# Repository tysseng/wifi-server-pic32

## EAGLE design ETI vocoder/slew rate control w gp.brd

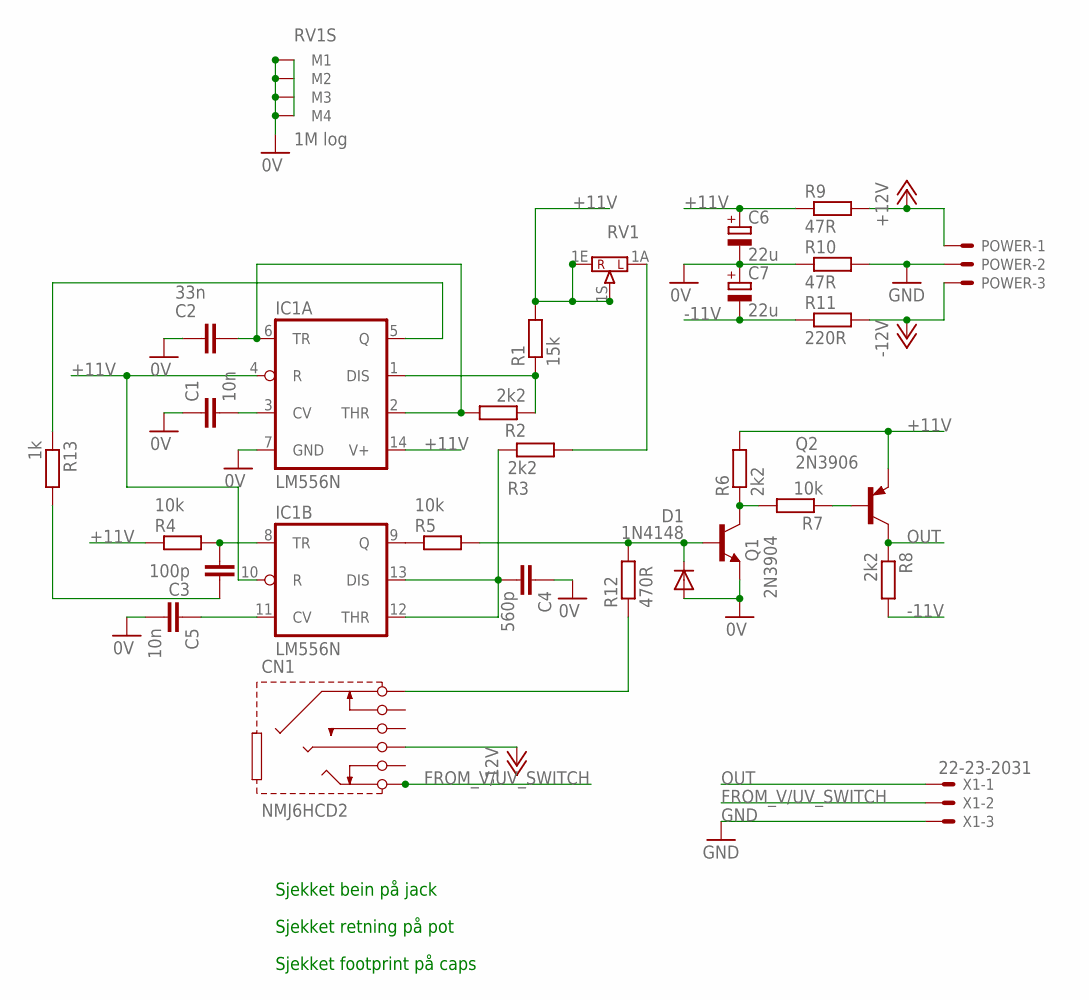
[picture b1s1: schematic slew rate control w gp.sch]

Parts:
C1, C5: 10n; C025-025X050
C2: 33n; C075-032X103
C3: 100p; C025-025X050
C4: 560p; C025-025X050
C6, C7: 22u; E2,5-5
CN1: NMJ6HCD2
D1: 1N4148; DO35-5J
IC1: LM556N; DIL14
POWER: KK-156-3
Q1: 2N3904; TO92
Q2: 2N3906; TO92
R1: 15k; 0207/7
R2, R3, R6, R8: 2k2; 0207/7
R4, R5, R7: 10k; 0207/7
R9, R10: 47R; 0207/7
R11: 220R; 0207/7
R12: 470R; 0207/7
R13: 1k; 0207/7
RV1: 1M log; POT16_W_BRACKET
X1: 22-23-2031

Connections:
0V: C1.1, C2.2, C4.1, C5.2, C6.-, C7.+, D1.A, IC1.7 (GND), Q1.3 (E), R10.1, RV1.M1, RV1.M2, RV1.M3, RV1.M4
+11V: C6.+, IC1.4 (R), IC1.10 (R), IC1.14 (V+), Q2.3 (E), R1.2, R4.1, R6.2, R9.1, RV1.1E, RV1.1S
+12V: POWER.1, R9.2
-11V: C7.-, R8.2, R11.1
-12V: CN1.R (RING), POWER.3, R11.2
FROM_V/UV_SWITCH: CN1.T (TIP), X1.2
GND: POWER.2, R10.2, X1.3
unnamed: C3.2, IC1.8 (TR), R4.2
unnamed: C2.1, IC1.2 (THR), IC1.6 (TR), R2.2
unnamed: C5.1, IC1.11 (CV)
unnamed: IC1.9 (Q), R5.1
unnamed: C4.2, IC1.12 (THR), IC1.13 (DIS), R3.1
unnamed: C3.1, R13.2
unnamed: IC1.5 (Q), R13.1
unnamed: R3.2, RV1.1A
unnamed: IC1.1 (DIS), R1.1, R2.1
unnamed: C1.2, IC1.3 (CV)
unnamed: D1.C, Q1.2 (B), R5.2, R12.2
unnamed: CN1.S (SLEEVE), R12.1
unnamed: Q1.1 (C), R6.1, R7.2
unnamed: Q2.2 (B), R7.1
OUT: Q2.1 (C), R8.1, X1.1

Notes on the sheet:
Sjekket retning på pot
Sjekket bein på jack
Sjekket footprint på caps

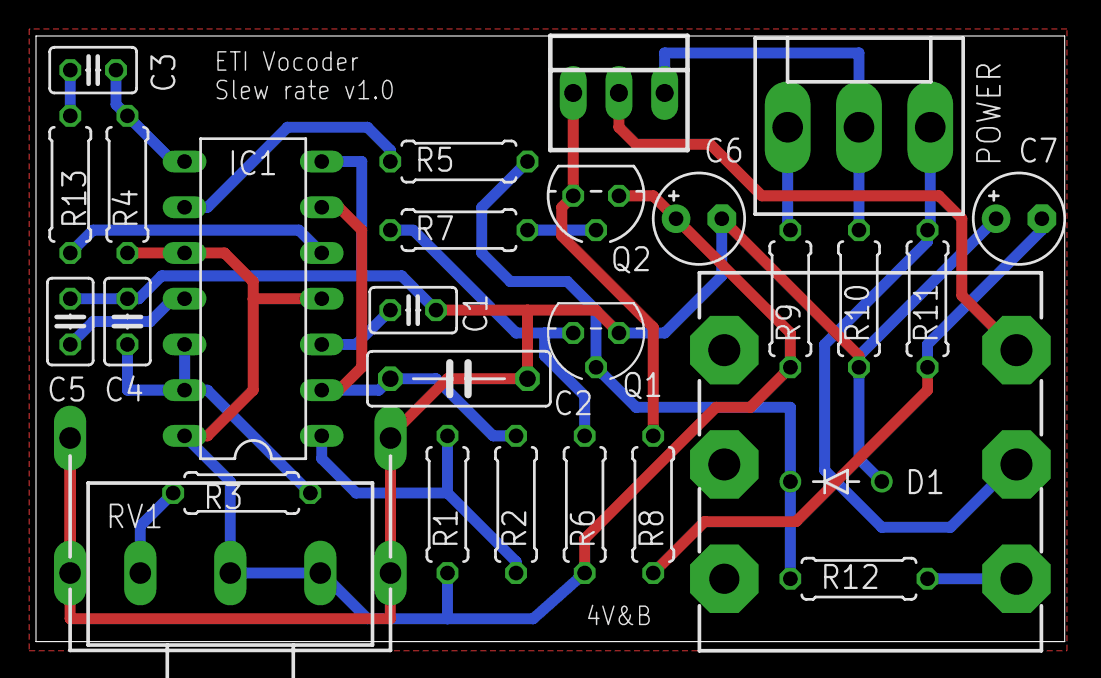
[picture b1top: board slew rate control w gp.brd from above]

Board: 2 copper layers, 57.1 x 33.6 mm, 28 parts (0 on the bottom side), 22 nets.

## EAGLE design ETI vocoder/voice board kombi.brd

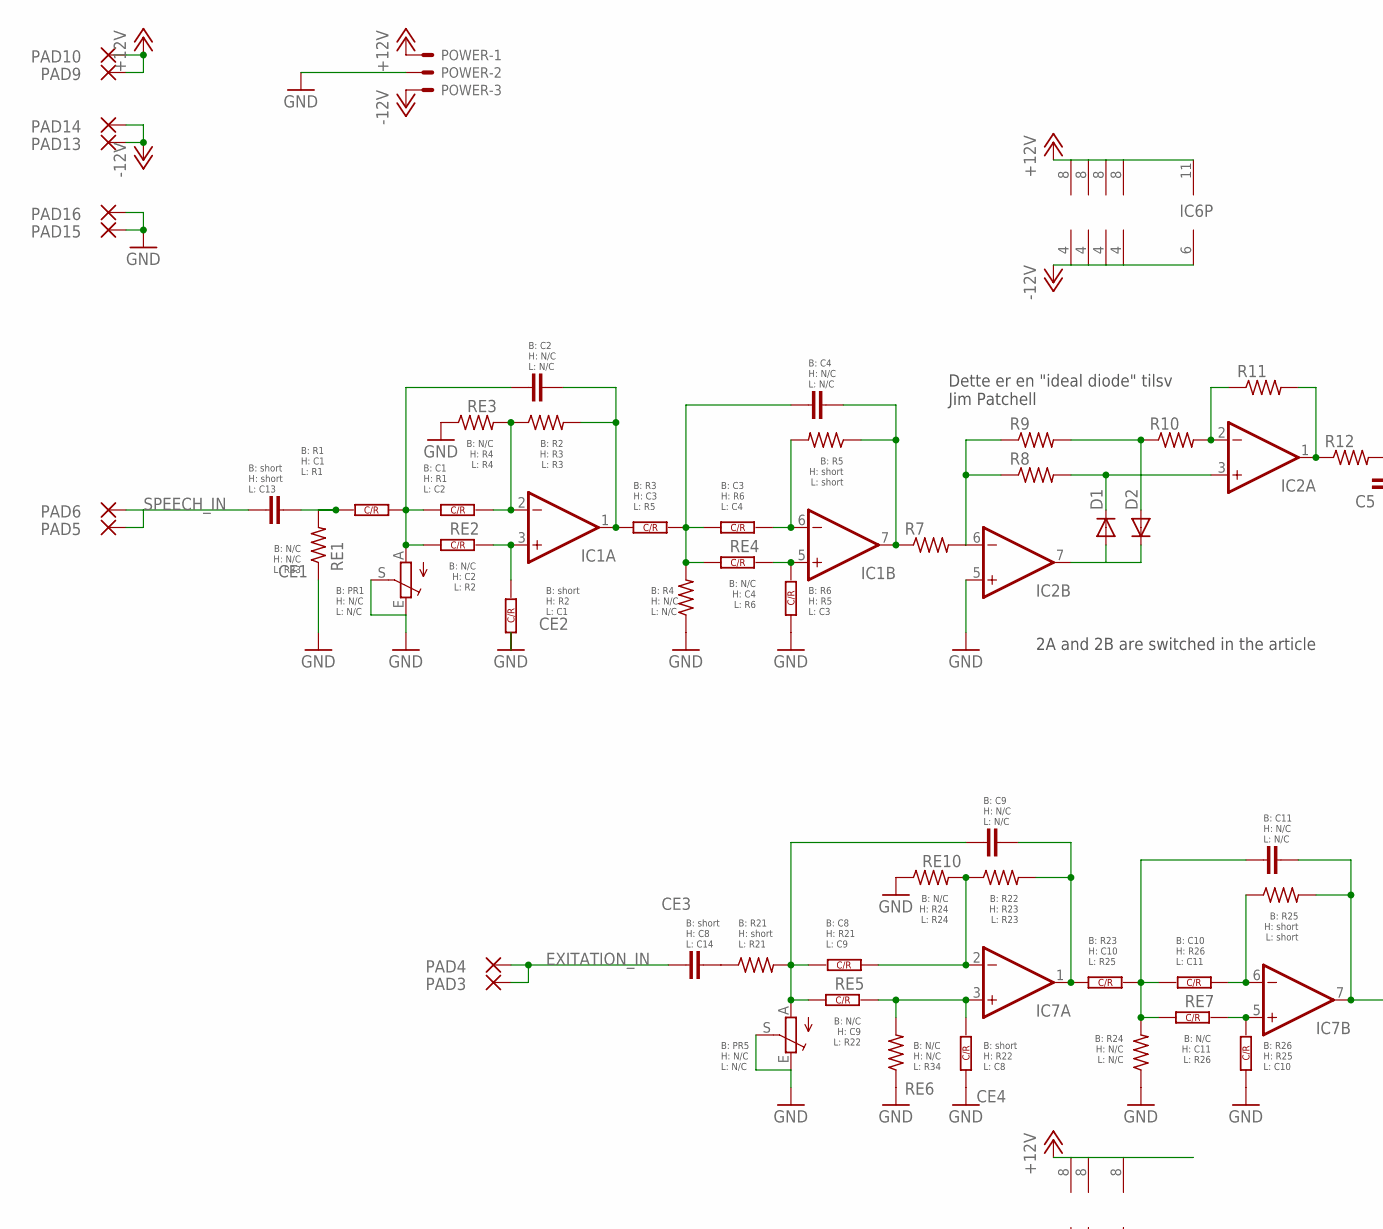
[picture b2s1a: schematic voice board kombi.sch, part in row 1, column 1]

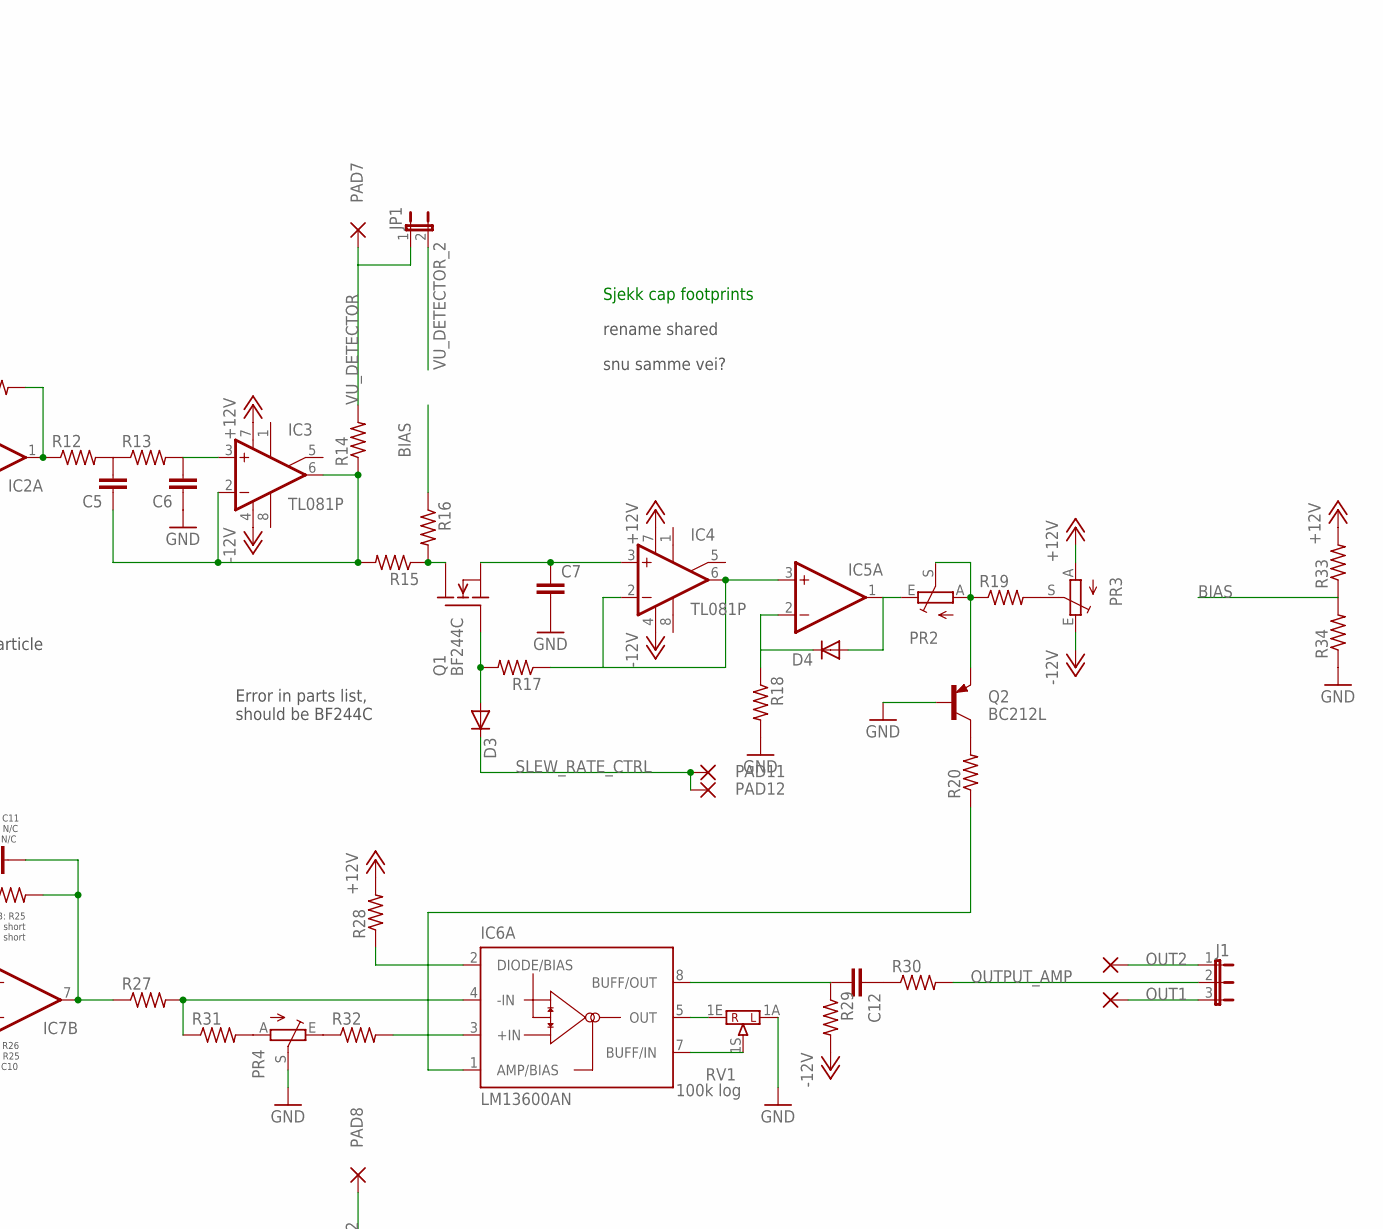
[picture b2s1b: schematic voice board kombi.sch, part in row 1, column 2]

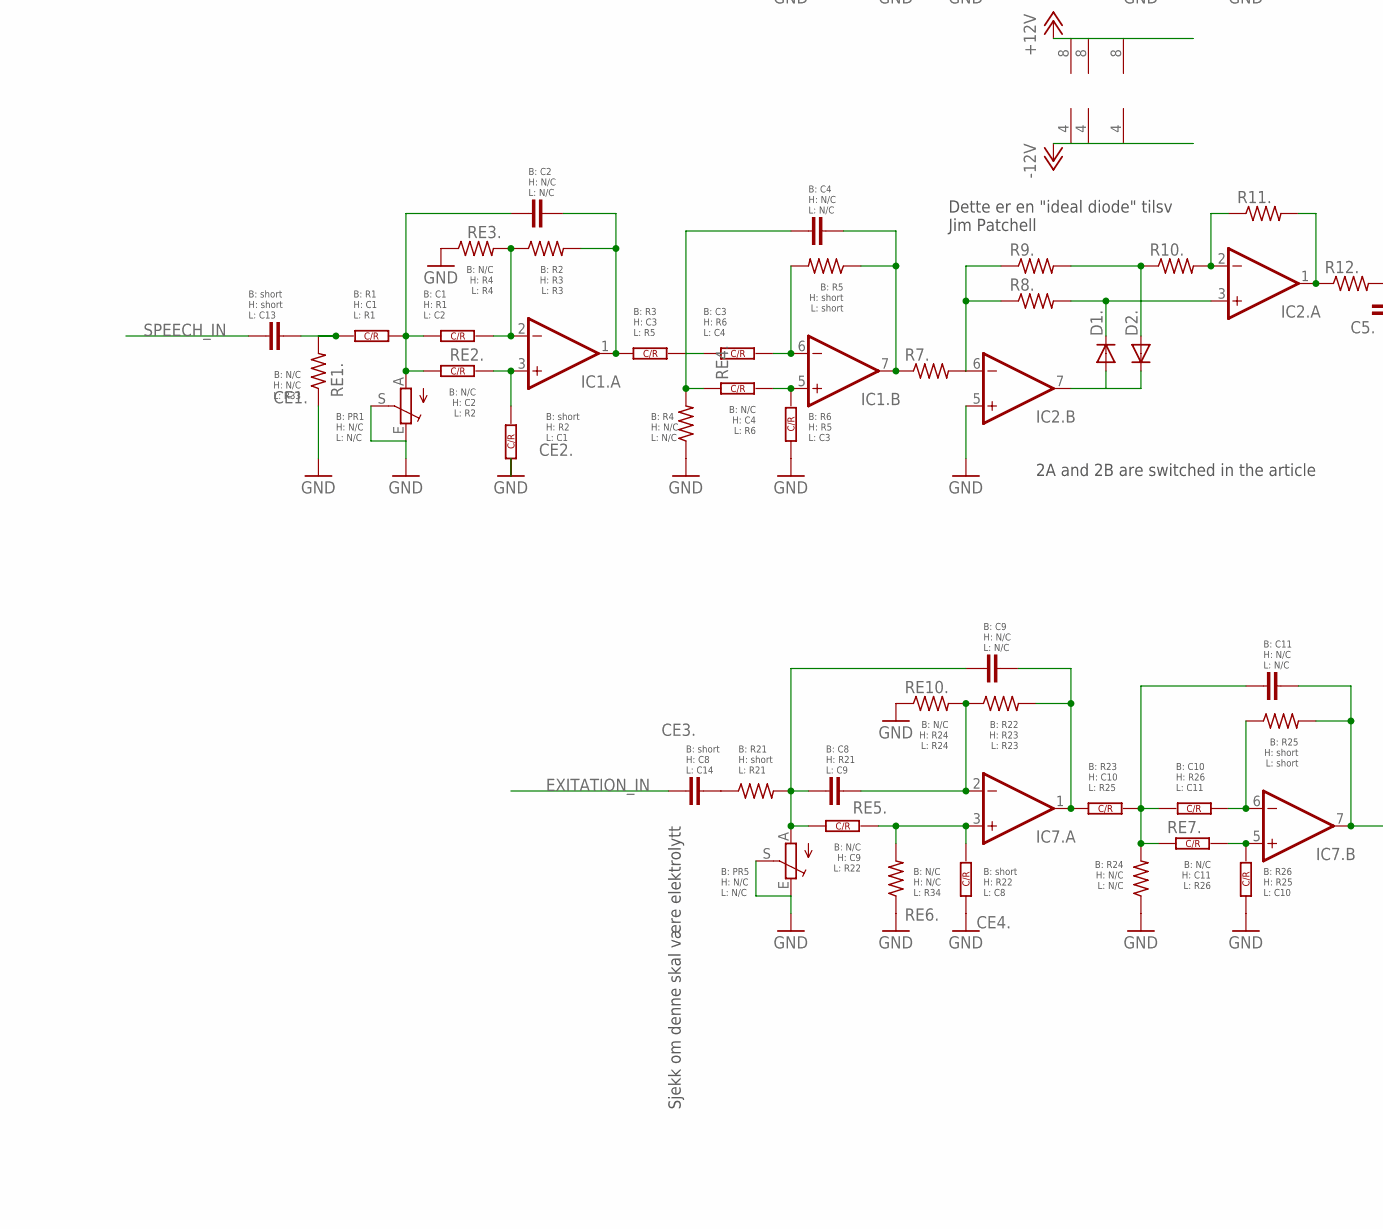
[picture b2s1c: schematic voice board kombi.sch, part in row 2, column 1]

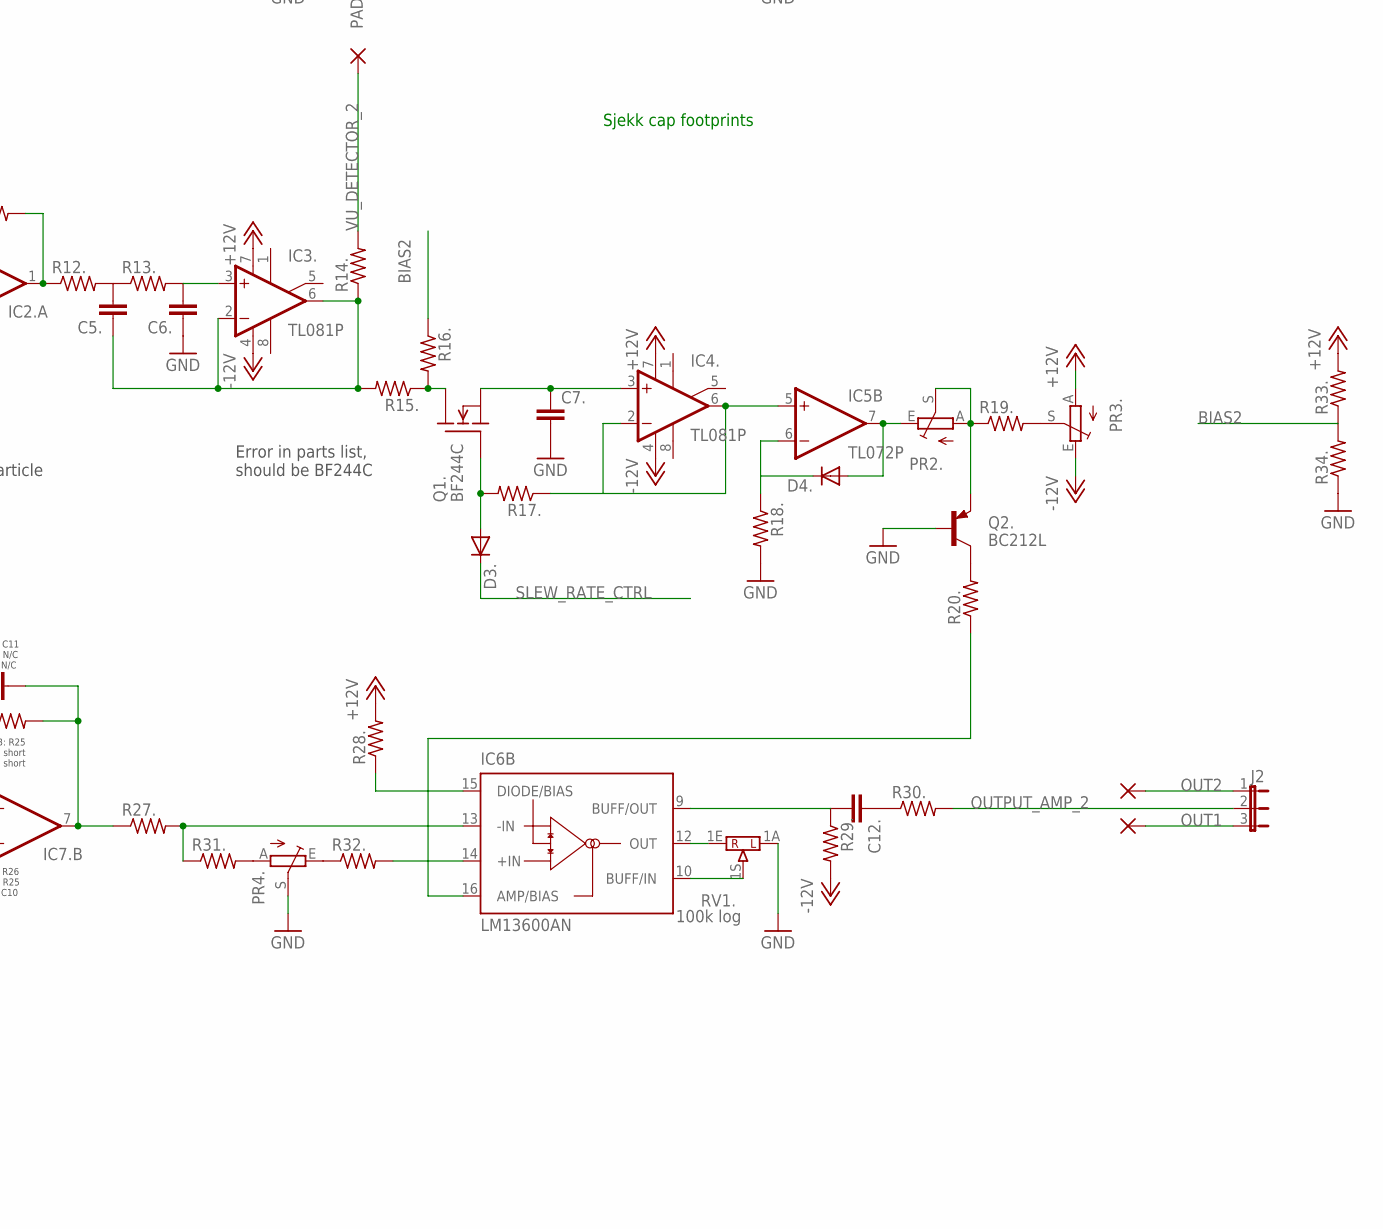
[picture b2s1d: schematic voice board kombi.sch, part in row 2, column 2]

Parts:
C1, C1., C3, C3., C8, C10, C10.: C-OR-R050_075-025X100; P050_075-025X100J
C2, C2., C4, C4., C5, C5., C6, C6., C7, C7., C8., C9, C9., C11, C11., C12, C12.: C-EU050_075-025X100; C050_075-025X100J
CE1, CE1., CE3, CE3.: C-EU050_075-025X100; C050_075-025X100J
CE2, CE2., CE4, CE4.: C-OR-R050_075-025X100; P050_075-025X100J
D1, D1., D2, D2., D3, D3., D4, D4.: DIODE-D-5; D-5
IC1, IC1., IC2, IC2., IC5, IC7, IC7.: TL072P; DIL08
IC3, IC3., IC4, IC4.: TL081P; DIL08
IC6: LM13600AN; DIL16
J1, J2: JP2E; JP2
JP1: JP1E; JP1
PAD1, PAD2, PAD3, PAD4, PAD5, PAD6, PAD7, PAD8, PAD9, PAD10, PAD11, PAD12, PAD13, PAD14, PAD15, PAD16, PAD17, PAD18: WIREPAD2,54/1,1; 2,54/1,1
POWER: KK-156-3
PR1, PR1., PR2, PR2., PR3, PR3., PR4, PR4., PR5, PR5.: TRIM_EU-CA9V; CA9V
Q1, Q1.: BF244C; TO-92
Q2, Q2.: BC212L; TO92-ECB
R1, R1., R3, R3., R6, R6., R23, R23., R26, R26.: C-OR-R050_075-025X100; P050_075-025X100J
R2, R2., R4, R4., R5, R5., R7, R7., R8, R8., R9, R9., R10, R10., R11, R11., R12, R12., R13, R13., R14, R14., R15, R15., R16, R16., R17, R17., R18, R18., R19, R19., R20, R20., R21, R21., R22, R22., R24, R24., R25, R25., R27, R27., R28, R28., R29, R29., R30, R30., R31, R31., R32, R32., R33, R33., R34, R34.: R-US_0207/7; 0207/7
RE1, RE1., RE3, RE3., RE6, RE6., RE10, RE10.: R-US_0207/7; 0207/7
RE2, RE2., RE4, RE4., RE5, RE5., RE7, RE7.: C-OR-R050_075-025X100; P050_075-025X100J
RV1, RV1.: 100k log; POT16_W_BRACKET

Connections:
+12V: IC1.8 (V+), IC1..8 (V+), IC2.8 (V+), IC2..8 (V+), IC3.7 (V+), IC3..7 (V+), IC4.7 (V+), IC4..7 (V+), IC5.8 (V+), IC6.11 (V+), IC7.8 (V+), IC7..8 (V+), PAD9.1, PAD10.1, POWER.1, PR3.A, PR3..A, R28.2, R28..2, R33.2, R33..2
-12V: IC1.4 (V-), IC1..4 (V-), IC2.4 (V-), IC2..4 (V-), IC3.4 (V-), IC3..4 (V-), IC4.4 (V-), IC4..4 (V-), IC5.4 (V-), IC6.6 (V-), IC7.4 (V-), IC7..4 (V-), PAD13.1, PAD14.1, POWER.3, PR3.E, PR3..E, R29.2, R29..2
BIAS: R16.1, R33.1, R34.2
BIAS2: R16..1, R33..1, R34..2
EXITATION_IN: CE3.1, CE3..1, PAD3.1, PAD4.1
GND: C6.1, C6..1, C7.2, C7.3 (2), C7..2, C7..3 (2), CE2.1, CE2..1, CE4.1, CE4..1, IC2.5 (+IN), IC2..5 (+IN), PAD15.1, PAD16.1, POWER.2, PR1.E, PR1.S, PR1..E, PR1..S, PR4.S, PR4..S, PR5.E, PR5.S, PR5..E, PR5..S, Q2.B, Q2..B, R4.1, R4..1, R6.1, R6..1, R18.2, R18..2, R24.1, R24..1, R26.1, R26..1, R34.1, R34..1, RE1.1, RE1..1, RE3.1, RE3..1, RE6.1, RE6..1, RE10.1, RE10..1, RV1.1A, RV1..1A
unnamed: C1.2, C1.3 (2), IC1.2 (-IN), R2.1, RE3.2
unnamed: C1.1, C2.1, PR1.A, R1.1, RE2.1
unnamed: C2.2, C2.3 (2), IC1.1 (OUT), R2.2, R3.1
unnamed: IC2.6 (-IN), R7.2, R8.1, R9.1
unnamed: C3.1, C4.1, R3.2, R3.3 (2), R4.2, RE4.1
unnamed: C3.2, C3.3 (2), IC1.6 (-IN), R5.2
unnamed: IC1.5 (+IN), R6.2, R6.3 (2), RE4.2, RE4.3 (2)
unnamed: C4.2, C4.3 (2), IC1.7 (OUT), R5.1, R7.1
unnamed: D1.C, IC2.3 (+IN), R8.2
unnamed: D1.A, D2.C, IC2.7 (OUT)
unnamed: D2.A, R9.2, R10.1
unnamed: IC2.2 (-IN), R10.2, R11.1
unnamed: IC2.1 (OUT), R11.2, R12.1
unnamed: C5.2, C5.3 (2), R12.2, R13.1
unnamed: C5.1, IC3.2 (-IN), IC3.6 (OUT), R14.1, R15.2
unnamed: C6.2, C6.3 (2), IC3.3 (+IN), R13.2
unnamed: Q1.3 (D), R15.1, R16.2
unnamed: C7.1, IC4.3 (+IN), Q1.1 (S)
unnamed: D3.A, Q1.2 (G), R17.2
unnamed: IC4.2 (-IN), IC4.6 (OUT), IC5.3 (+IN), R17.1
unnamed: D4.C, IC5.2 (-IN), R18.1
unnamed: D4.A, IC5.1 (OUT), PR2.E
unnamed: PR2.A, PR2.S, Q2.E, R19.1
unnamed: PR3.S, R19.2
unnamed: Q2.C, R20.2
unnamed: PR4.A, R31.2
unnamed: C8.2, C8.3 (2), C9.2, C9.3 (2), PR5.A, R21.2, RE5.1
unnamed: C10.2, C10.3 (2), C11.2, C11.3 (2), R23.2, R23.3 (2), R24.2, RE7.1
unnamed: C8.1, IC7.2 (-IN), R22.1, RE10.2
unnamed: C9.1, IC7.1 (OUT), R22.2, R23.1
unnamed: C10.1, IC7.6 (-IN), R25.1
unnamed: IC7.5 (+IN), R26.2, R26.3 (2), RE7.2, RE7.3 (2)
unnamed: C12.2, C12.3 (2), IC6.8 (BUFF/OUT), R29.1
unnamed: C12.1, R30.1
unnamed: C11.1, IC7.7 (OUT), R25.2, R27.1
unnamed: PR4.E, R32.1
unnamed: IC6.3 (+IN), R32.2
unnamed: IC6.2 (DIODE/BIAS), R28.1
unnamed: IC6.4 (-IN), R27.2, R31.1
unnamed: IC6.1 (AMP/BIAS), R20.1
unnamed: IC6.5 (OUT), RV1.1E
unnamed: IC6.7 (BUFF/IN), RV1.1S
unnamed: CE1.1, R1.2, R1.3 (2), RE1.2
unnamed: CE2.2, CE2.3 (2), IC1.3 (+IN), RE2.2, RE2.3 (2)
unnamed: CE3.2, CE3.3 (2), R21.1
unnamed: CE4.2, CE4.3 (2), IC7.3 (+IN), RE5.2, RE5.3 (2), RE6.2
unnamed: C1..2, C1..3 (2), IC1..2 (-IN), R2..1, RE3..2
unnamed: C1..1, C2..1, PR1..A, R1..1, RE2..1
unnamed: C2..2, C2..3 (2), IC1..1 (OUT), R2..2, R3..1
unnamed: C3..1, C4..1, R3..2, R3..3 (2), R4..2, RE4..1
unnamed: C3..2, C3..3 (2), IC1..6 (-IN), R5..2
unnamed: IC1..5 (+IN), R6..2, R6..3 (2), RE4..2, RE4..3 (2)
unnamed: C4..2, C4..3 (2), IC1..7 (OUT), R5..1, R7..1
unnamed: IC2..6 (-IN), R7..2, R8..1, R9..1
unnamed: D1..C, IC2..3 (+IN), R8..2
unnamed: D1..A, D2..C, IC2..7 (OUT)
unnamed: D2..A, R9..2, R10..1
unnamed: IC2..2 (-IN), R10..2, R11..1
unnamed: IC2..1 (OUT), R11..2, R12..1
unnamed: C5..2, C5..3 (2), R12..2, R13..1
unnamed: C5..1, IC3..2 (-IN), IC3..6 (OUT), R14..1, R15..2
unnamed: C6..2, C6..3 (2), IC3..3 (+IN), R13..2
unnamed: Q1..3 (D), R15..1, R16..2
unnamed: C7..1, IC4..3 (+IN), Q1..1 (S)
unnamed: D3..A, Q1..2 (G), R17..2
unnamed: IC4..2 (-IN), IC4..6 (OUT), IC5.5 (+IN), R17..1
unnamed: D4..C, IC5.6 (-IN), R18..1
unnamed: D4..A, IC5.7 (OUT), PR2..E
unnamed: PR2..A, PR2..S, Q2..E, R19..1
unnamed: PR3..S, R19..2
unnamed: Q2..C, R20..2
unnamed: PR4..A, R31..2
unnamed: C8..2, C8..3 (2), C9..2, C9..3 (2), PR5..A, R21..2, RE5..1
unnamed: C10..2, C10..3 (2), C11..2, C11..3 (2), R23..2, R23..3 (2), R24..2, RE7..1
unnamed: C8..1, IC7..2 (-IN), R22..1, RE10..2
unnamed: C9..1, IC7..1 (OUT), R22..2, R23..1
unnamed: C11..1, IC7..7 (OUT), R25..2, R27..1
unnamed: PR4..E, R32..1
unnamed: IC6.14 (+IN), R32..2
unnamed: IC6.15 (DIODE/BIAS), R28..1
unnamed: IC6.13 (-IN), R27..2, R31..1
unnamed: IC6.16 (AMP/BIAS), R20..1
unnamed: IC6.10 (BUFF/IN), RV1..1S
unnamed: C12..2, C12..3 (2), IC6.9 (BUFF/OUT), R29..1
unnamed: C12..1, R30..1
unnamed: C10..1, IC7..6 (-IN), R25..1
unnamed: IC7..5 (+IN), R26..2, R26..3 (2), RE7..2, RE7..3 (2)
unnamed: CE1..1, R1..2, R1..3 (2), RE1..2
unnamed: CE2..2, CE2..3 (2), IC1..3 (+IN), RE2..2, RE2..3 (2)
unnamed: CE3..2, CE3..3 (2), R21..1
unnamed: CE4..2, CE4..3 (2), IC7..3 (+IN), RE5..2, RE5..3 (2), RE6..2
unnamed: IC6.12 (OUT), RV1..1E
OUT1: J1.3, J2.3, PAD1.1, PAD2.1
OUT2: J1.1, J2.1, PAD17.1, PAD18.1
OUTPUT_AMP: J1.2, R30.2
OUTPUT_AMP_2: J2.2, R30..2
SLEW_RATE_CTRL: D3.C, D3..C, PAD11.1, PAD12.1
SPEECH_IN: CE1.2, CE1.3 (2), CE1..2, CE1..3 (2), PAD5.1, PAD6.1
VU_DETECTOR: JP1.1, PAD7.1, R14.2
VU_DETECTOR_2: JP1.2, PAD8.1, R14..2

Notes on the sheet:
Dette er en "ideal diode" tilsv Jim Patchell
B: short H: short L: C13
B: R1 H: C1 L: R1
B: PR1 H: N/C L: N/C
B: C1 H: R1 L: C2
B: C2 H: N/C L: N/C
B: C4 H: N/C L: N/C
B: R2 H: R3 L: R3
B: R3 H: C3 L: R5
B: R4 H: N/C L: N/C
B: C3 H: R6 L: C4
B: R6 H: R5 L: C3
B: R5 H: short L: short
B: N/C H: R4 L: R4
B: short H: R2 L: C1
B: N/C H: C2 L: R2
B: N/C H: N/C L: R33
B: short H: C8 L: C14
B: R21 H: short L: R21
B: C8 H: R21 L: C9
B: R22 H: R23 L: R23
B: C9 H: N/C L: N/C
B: C10 H: R26 L: C11
B: R23 H: C10 L: R25
B: N/C H: N/C L: R34
B: R24 H: N/C L: N/C
B: R26 H: R25 L: C10
B: C11 H: N/C L: N/C
B: R25 H: short L: short
B: N/C H: C9 L: R22
B: short H: R22 L: C8
B: N/C H: C4 L: R6
B: N/C H: C11 L: R26
B: PR5 H: N/C L: N/C
B: N/C H: R24 L: R24
Sjekk cap footprints
2A and 2B are switched in the article
Error in parts list, should be BF244C
Sjekk om denne skal være elektrolytt
rename shared

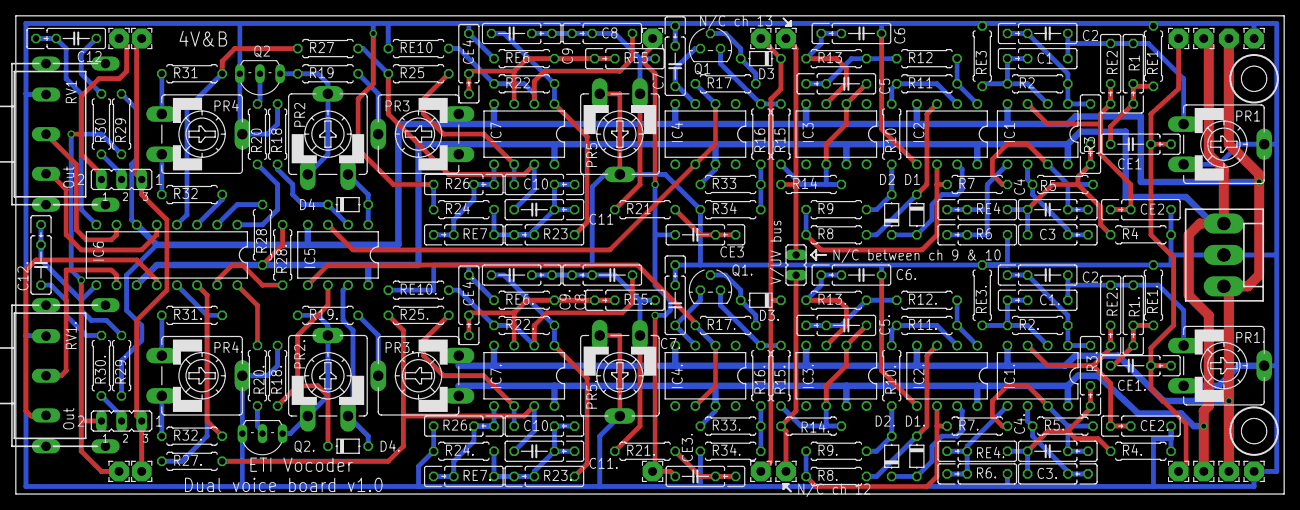
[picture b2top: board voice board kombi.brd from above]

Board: 2 copper layers, 160.0 x 60.3 mm, 174 parts (1 on the bottom side), 106 nets.

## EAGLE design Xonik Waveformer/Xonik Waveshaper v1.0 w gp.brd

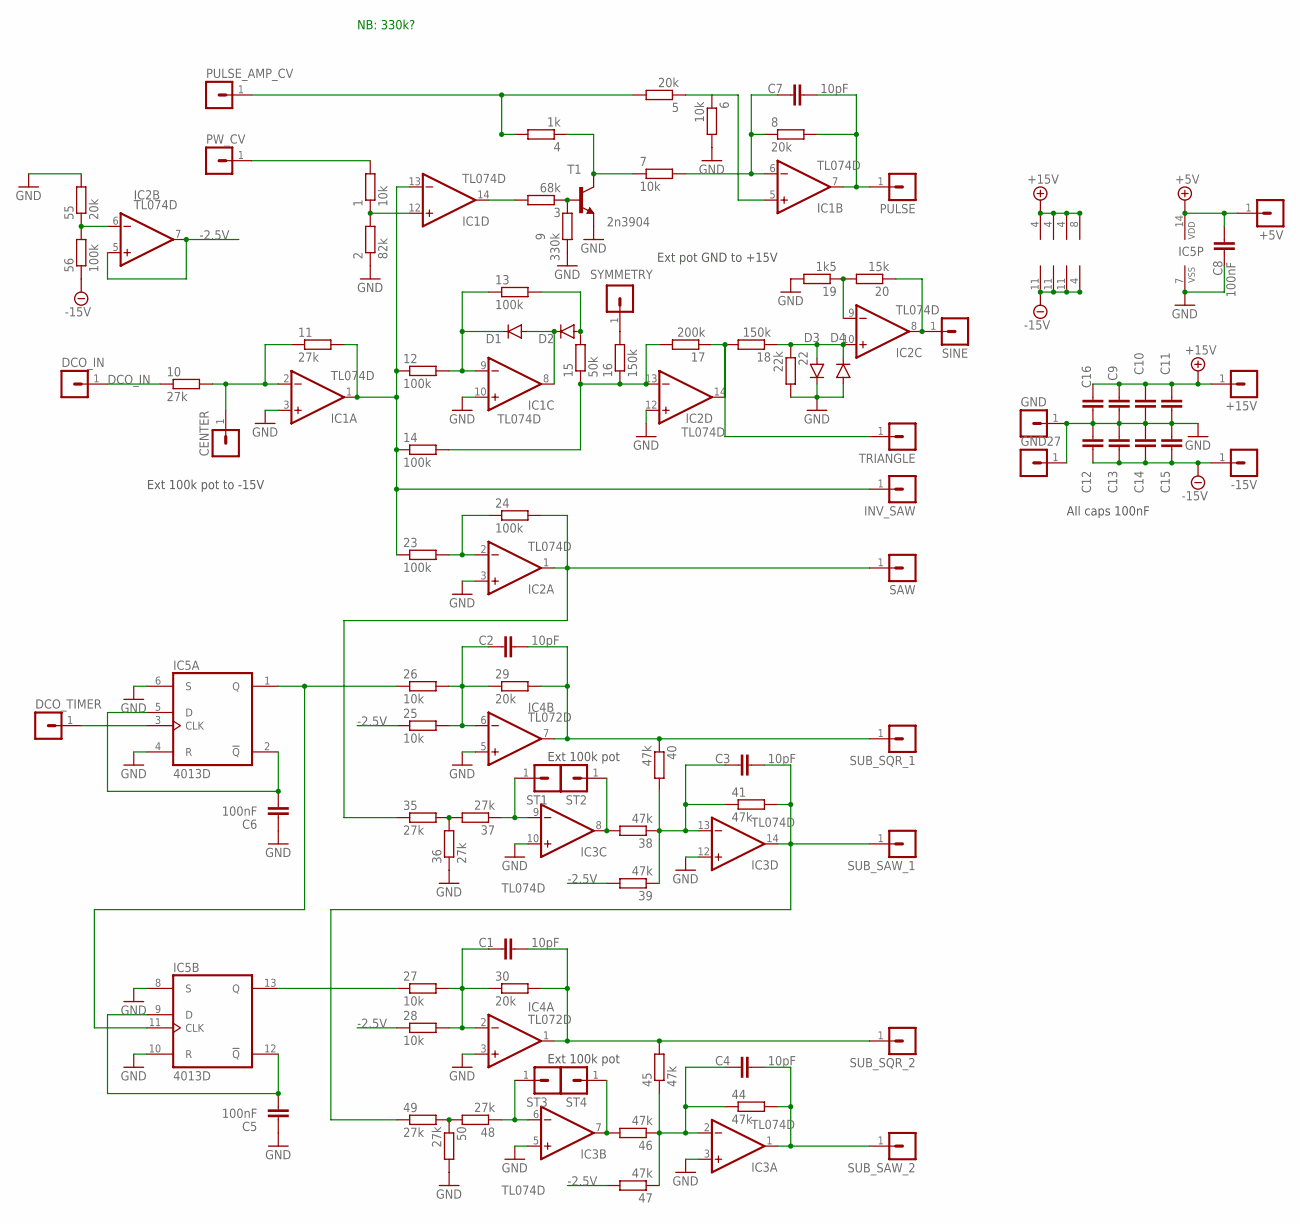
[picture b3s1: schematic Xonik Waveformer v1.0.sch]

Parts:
1, 6, 7, 25, 26, 27, 28: 10k; R0805
2: 82k; R0805
3: 68k; R0805
4: 1k; R0805
5, 8, 29, 30, 55: 20k; R0805
9: 330k; R0805
10, 11, 35, 36, 37, 48, 49, 50: 27k; R0805
12, 13, 14, 23, 24, 56: 100k; R0805
15: 50k; R0805
16, 18: 150k; R0805
17: 200k; R0805
19: 1k5; R0805
20: 15k; R0805
22: 22k; R0805
38, 39, 40, 41, 44, 45, 46, 47: 47k; R0805
+5V, +15V: MA01-1JP; SIP-PIN01-1J
-15V: MA01-1JP; SIP-PIN01-1J
C1, C2, C3, C4, C7: 10pF; C0805
C5, C6, C8: 100nF; C0805
C9, C10, C11, C12, C13, C14, C15, C16: 100nF; C0603K
CENTER: MA01-1JP; SIP-PIN01-1J
D1, D2, D3, D4: 1N41480805; D0805-J
DCO_IN: MA01-1JP; SIP-PIN01-1J
DCO_TIMER: MA01-1JP; SIP-PIN01-1J
GND, GND27: MA01-1JP; SIP-PIN01-1J
IC1, IC2, IC3: TL074D; SO14
IC4: TL072D; SO08J
IC5: 4013D; SO14J
INV_SAW: MA01-1JP; SIP-PIN01-1J
PULSE: MA01-1JP; SIP-PIN01-1J
PULSE_AMP_CV: MA01-1JP; SIP-PIN01-1J
PW_CV: MA01-1JP; SIP-PIN01-1J
SAW: MA01-1JP; SIP-PIN01-1J
SINE: MA01-1JP; SIP-PIN01-1J
ST1, ST2, ST3, ST4: MA01-1JP; SIP-PIN01-1J
SUB_SAW_1, SUB_SAW_2: MA01-1JP; SIP-PIN01-1J
SUB_SQR_1, SUB_SQR_2: MA01-1JP; SIP-PIN01-1J
SYMMETRY: MA01-1JP; SIP-PIN01-1J
T1: 2n3904; SOT23-BEC
TRIANGLE: MA01-1JP; SIP-PIN01-1J

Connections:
+5V: +5V.1, C8.2, IC5.14 (VDD)
+15V: +15V.1, C9.2, C10.2, C11.2, C16.2, IC1.4 (V+), IC2.4 (V+), IC3.4 (V+), IC4.8 (V+)
-2.5V: 25.1, 28.1, 39.2, 47.2, IC2.5 (+IN), IC2.7 (OUT)
-15V: 56.1, -15V.1, C12.1, C13.1, C14.1, C15.1, IC1.11 (V-), IC2.11 (V-), IC3.11 (V-), IC4.4 (V-)
AMP_CV: 4.2, 5.2, PULSE_AMP_CV.1
DCO_IN: 10.1, DCO_IN.1
GND: 2.1, 6.2, 9.2, 19.2, 22.2, 36.1, 50.2, 55.2, C5.1, C6.1, C8.1, C9.1, C10.1, C11.1, C12.2, C13.2, C14.2, C15.2, C16.1, D3.C, D4.A, GND.1, GND27.1, IC1.3 (+IN), IC1.10 (+IN), IC2.3 (+IN), IC2.12 (+IN), IC3.3 (+IN), IC3.5 (+IN), IC3.10 (+IN), IC3.12 (+IN), IC4.3 (+IN), IC4.5 (+IN), IC5.4 (R), IC5.6 (S), IC5.7 (VSS), IC5.8 (S), IC5.10 (R), T1.E
unnamed: 1.1, 2.2, IC1.12 (+IN)
unnamed: 3.2, IC1.14 (OUT)
unnamed: 3.1, 9.1, T1.B
unnamed: 4.1, 7.1, T1.C
unnamed: 5.1, 6.1, IC1.5 (+IN)
unnamed: 7.2, 8.1, C7.1, IC1.6 (-IN)
unnamed: 8.2, C7.2, IC1.7 (OUT), PULSE.1
unnamed: 11.2, 12.1, 14.1, 23.1, IC1.1 (OUT), IC1.13 (-IN), INV_SAW.1
unnamed: 10.2, 11.1, CENTER.1, IC1.2 (-IN)
unnamed: 12.2, 13.1, D1.C, IC1.9 (-IN)
unnamed: D1.A, D2.C, IC1.8 (OUT)
unnamed: 13.2, 15.2, D2.A
unnamed: 14.2, 15.1, 16.1, 17.2, IC2.13 (-IN)
unnamed: 23.2, 24.1, IC2.2 (-IN)
unnamed: 24.2, 35.1, IC2.1 (OUT), SAW.1
unnamed: 25.2, 26.2, 29.1, C2.1, IC4.6 (-IN)
unnamed: 46.2, IC3.7 (OUT), ST4.1
unnamed: 48.2, 49.2, 50.1
unnamed: 27.2, 28.2, 30.1, C1.1, IC4.2 (-IN)
unnamed: 35.2, 36.2, 37.2
unnamed: 37.1, IC3.9 (-IN), ST1.1
unnamed: 38.1, 39.1, 40.2, 41.1, C3.1, IC3.13 (-IN)
unnamed: 41.2, 49.1, C3.2, IC3.14 (OUT), SUB_SAW_1.1
unnamed: 48.1, IC3.6 (-IN), ST3.1
unnamed: 44.1, 45.1, 46.1, 47.1, C4.1, IC3.2 (-IN)
unnamed: 44.2, C4.2, IC3.1 (OUT), SUB_SAW_2.1
unnamed: C6.2, IC5.2 (!Q), IC5.5 (D)
unnamed: 55.1, 56.2, IC2.6 (-IN)
unnamed: C5.2, IC5.9 (D), IC5.12 (!Q)
unnamed: 19.1, 20.2, IC2.9 (-IN)
unnamed: 16.2, SYMMETRY.1
unnamed: 17.1, 18.2, IC2.14 (OUT), TRIANGLE.1
unnamed: 18.1, 22.1, D3.A, D4.C, IC2.10 (+IN)
unnamed: 20.1, IC2.8 (OUT), SINE.1
unnamed: 38.2, IC3.8 (OUT), ST2.1
PW_CV: 1.2, PW_CV.1
SQR: DCO_TIMER.1, IC5.3 (CLK)

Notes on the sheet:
NB: 330k?
All caps 100nF
Ext 100k pot to -15V
Ext pot GND to +15V
Ext 100k pot

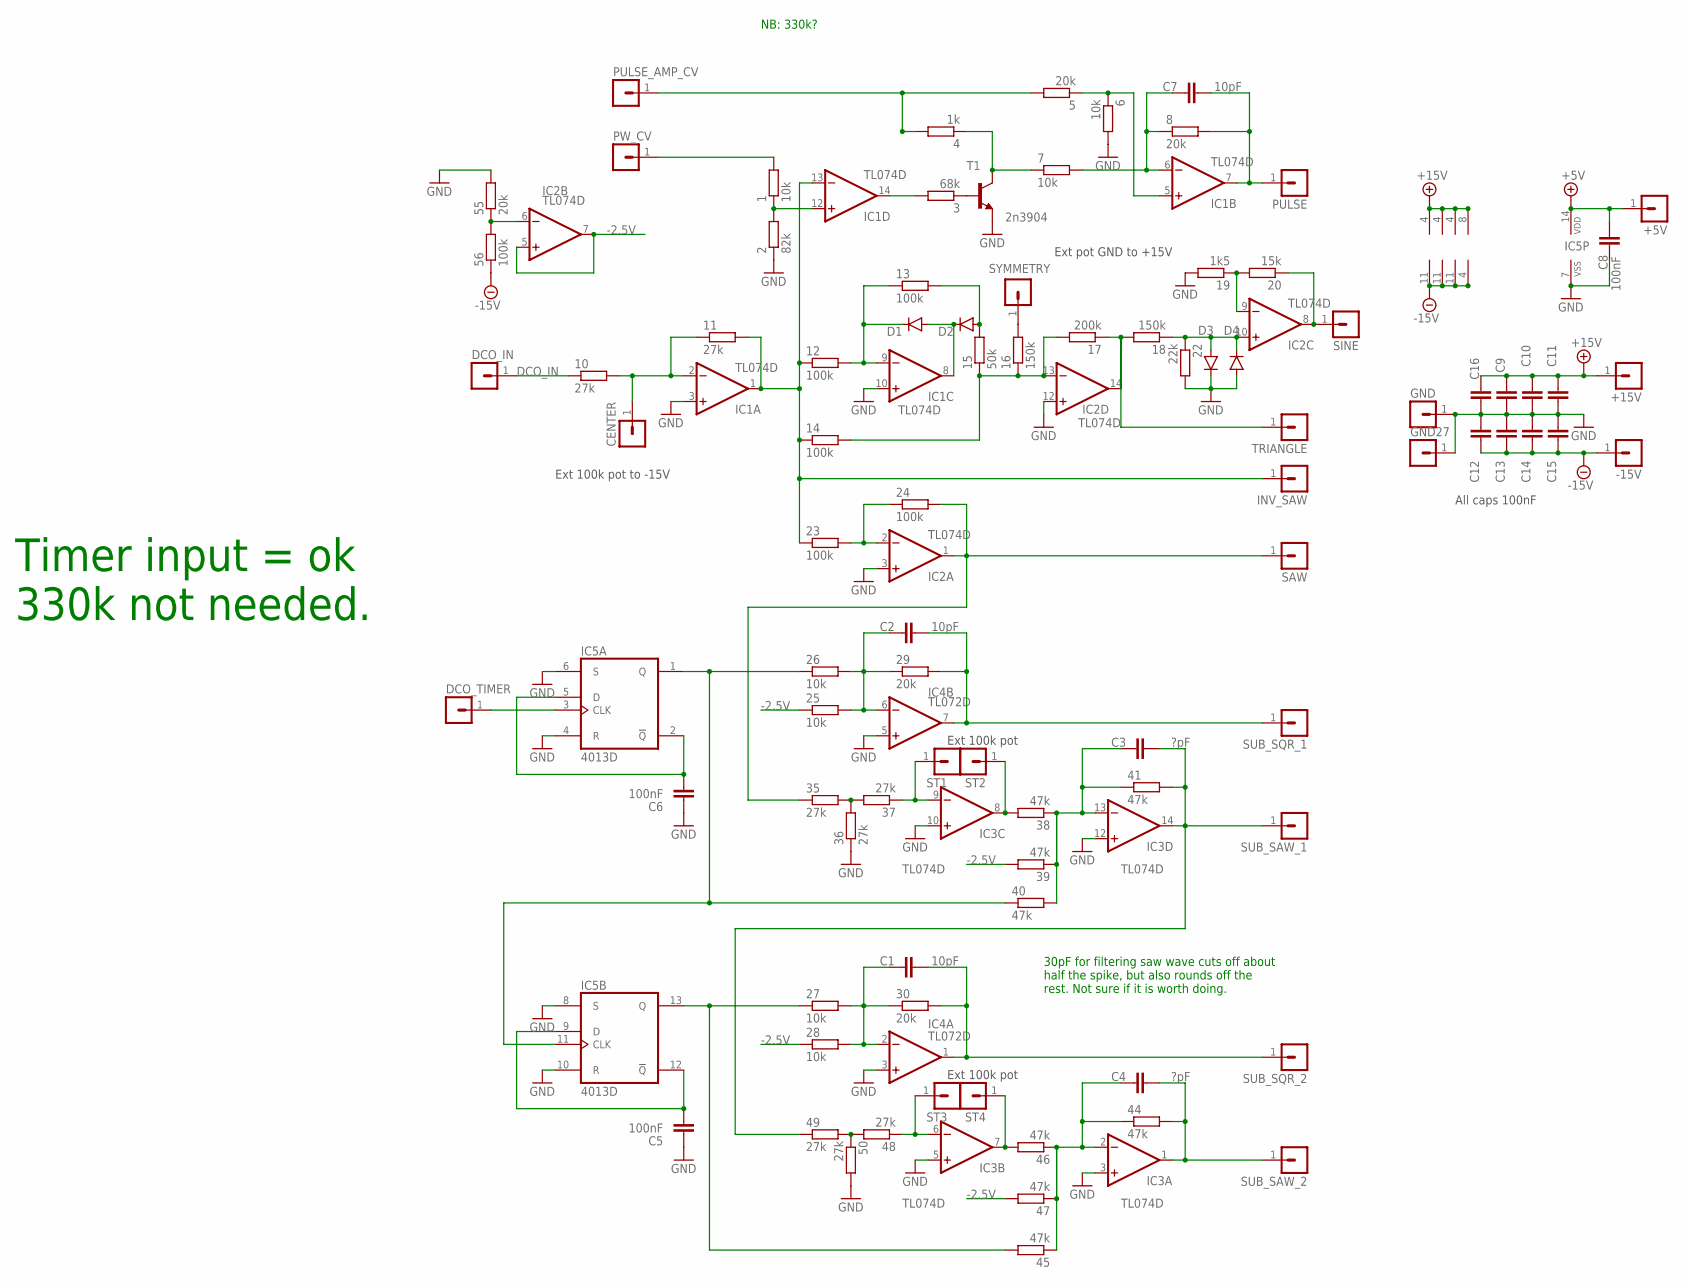
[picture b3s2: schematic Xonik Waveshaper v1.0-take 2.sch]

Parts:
1, 6, 7, 25, 26, 27, 28: 10k; R0805
2: 82k; R0805
3: 68k; R0805
4: 1k; R0805
5, 8, 29, 30, 55: 20k; R0805
10, 11, 35, 36, 37, 48, 49, 50: 27k; R0805
12, 13, 14, 23, 24, 56: 100k; R0805
15: 50k; R0805
16, 18: 150k; R0805
17: 200k; R0805
19: 1k5; R0805
20: 15k; R0805
22: 22k; R0805
38, 39, 40, 41, 44, 45, 46, 47: 47k; R0805
+5V, +15V: MA01-1JP; SIP-PIN01-1J
-15V: MA01-1JP; SIP-PIN01-1J
C1, C2, C7: 10pF; C0805
C3, C4: ?pF; C0805
C5, C6, C8: 100nF; C0805
C9, C10, C11, C12, C13, C14, C15, C16: 100nF; C0603K
CENTER: MA01-1JP; SIP-PIN01-1J
D1, D2, D3, D4: 1N41480805; D0805-J
DCO_IN: MA01-1JP; SIP-PIN01-1J
DCO_TIMER: MA01-1JP; SIP-PIN01-1J
GND, GND27: MA01-1JP; SIP-PIN01-1J
IC1, IC2, IC3: TL074D; SO14
IC4: TL072D; SO08J
IC5: 4013D; SO14J
INV_SAW: MA01-1JP; SIP-PIN01-1J
PULSE: MA01-1JP; SIP-PIN01-1J
PULSE_AMP_CV: MA01-1JP; SIP-PIN01-1J
PW_CV: MA01-1JP; SIP-PIN01-1J
SAW: MA01-1JP; SIP-PIN01-1J
SINE: MA01-1JP; SIP-PIN01-1J
ST1, ST2, ST3, ST4: MA01-1JP; SIP-PIN01-1J
SUB_SAW_1, SUB_SAW_2: MA01-1JP; SIP-PIN01-1J
SUB_SQR_1, SUB_SQR_2: MA01-1JP; SIP-PIN01-1J
SYMMETRY: MA01-1JP; SIP-PIN01-1J
T1: 2n3904; SOT23-BEC
TRIANGLE: MA01-1JP; SIP-PIN01-1J

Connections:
+5V: +5V.1, C8.2, IC5.14 (VDD)
+15V: +15V.1, C9.2, C10.2, C11.2, C16.2, IC1.4 (V+), IC2.4 (V+), IC3.4 (V+), IC4.8 (V+)
-2.5V: 25.1, 28.1, 39.2, 47.2, IC2.5 (+IN), IC2.7 (OUT)
-15V: 56.1, -15V.1, C12.1, C13.1, C14.1, C15.1, IC1.11 (V-), IC2.11 (V-), IC3.11 (V-), IC4.4 (V-)
AMP_CV: 4.2, 5.2, PULSE_AMP_CV.1
DCO_IN: 10.1, DCO_IN.1
GND: 2.1, 6.2, 19.2, 22.2, 36.1, 50.2, 55.2, C5.1, C6.1, C8.1, C9.1, C10.1, C11.1, C12.2, C13.2, C14.2, C15.2, C16.1, D3.C, D4.A, GND.1, GND27.1, IC1.3 (+IN), IC1.10 (+IN), IC2.3 (+IN), IC2.12 (+IN), IC3.3 (+IN), IC3.5 (+IN), IC3.10 (+IN), IC3.12 (+IN), IC4.3 (+IN), IC4.5 (+IN), IC5.4 (R), IC5.6 (S), IC5.7 (VSS), IC5.8 (S), IC5.10 (R), T1.E; also elsewhere on the board
unnamed: 1.1, 2.2, IC1.12 (+IN)
unnamed: 3.2, IC1.14 (OUT)
unnamed 9: 3.1, T1.B; also elsewhere on the board
unnamed: 4.1, 7.1, T1.C
unnamed: 5.1, 6.1, IC1.5 (+IN)
unnamed: 7.2, 8.1, C7.1, IC1.6 (-IN)
unnamed: 8.2, C7.2, IC1.7 (OUT), PULSE.1
unnamed: 11.2, 12.1, 14.1, 23.1, IC1.1 (OUT), IC1.13 (-IN), INV_SAW.1
unnamed: 10.2, 11.1, CENTER.1, IC1.2 (-IN)
unnamed: 12.2, 13.1, D1.C, IC1.9 (-IN)
unnamed: D1.A, D2.C, IC1.8 (OUT)
unnamed: 13.2, 15.2, D2.A
unnamed: 14.2, 15.1, 16.1, 17.2, IC2.13 (-IN)
unnamed: 23.2, 24.1, IC2.2 (-IN)
unnamed: 24.2, 35.1, IC2.1 (OUT), SAW.1
unnamed: 25.2, 26.2, 29.1, C2.1, IC4.6 (-IN)
unnamed: 46.2, IC3.7 (OUT), ST4.1
unnamed: 48.2, 49.2, 50.1
unnamed: 27.2, 28.2, 30.1, C1.1, IC4.2 (-IN)
unnamed: 35.2, 36.2, 37.2
unnamed: 37.1, IC3.9 (-IN), ST1.1
unnamed: 38.1, 39.1, 40.2, 41.1, C3.1, IC3.13 (-IN)
unnamed: 41.2, 49.1, C3.2, IC3.14 (OUT), SUB_SAW_1.1
unnamed: 48.1, IC3.6 (-IN), ST3.1
unnamed: 44.1, 45.1, 46.1, 47.1, C4.1, IC3.2 (-IN)
unnamed: 44.2, C4.2, IC3.1 (OUT), SUB_SAW_2.1
unnamed: C6.2, IC5.2 (!Q), IC5.5 (D)
unnamed: 55.1, 56.2, IC2.6 (-IN)
unnamed: C5.2, IC5.9 (D), IC5.12 (!Q)
unnamed: 19.1, 20.2, IC2.9 (-IN)
unnamed: 16.2, SYMMETRY.1
unnamed: 17.1, 18.2, IC2.14 (OUT), TRIANGLE.1
unnamed: 18.1, 22.1, D3.A, D4.C, IC2.10 (+IN)
unnamed: 20.1, IC2.8 (OUT), SINE.1
unnamed: 38.2, IC3.8 (OUT), ST2.1
PW_CV: 1.2, PW_CV.1
SQR: DCO_TIMER.1, IC5.3 (CLK)

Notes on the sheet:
NB: 330k?
All caps 100nF
Ext 100k pot to -15V
Ext pot GND to +15V
Ext 100k pot
Timer input = ok 330k not needed.
30pF for filtering saw wave cuts off about half the spike, but also rounds off the rest. Not sure if it is worth doing.

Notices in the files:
parts and their libraries:
audio: Copyright (C) 2008, Bob Starr
